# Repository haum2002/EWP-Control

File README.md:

# SmartCoolingv2.1 / EWP Controller
### Super Intelligent Thermal Management System | ESP32-S3 Powered

> **SmartCooling** bukan sekadar pengawal suhu. Ia adalah sistem **Super Intelligence (SI)** yang sedar situasi, mampu memprediksi kegagalan, menahan serangan siber-logik, dan beroperasi secara autonomi dalam persekitaran ekstrem. Dibina dengan arkitektur modular hibrid untuk kestabilan maksimum.

---

## 🚀 Ciri Utama & Keunikan

### 🧠 Super Intelligence (SI) Core
Bukan AI biasa. SI kami menggabungkan kawalan adaptif, model fizik termodinamik, dan analisis risiko masa nyata.
- **Adaptive PID & Feed-Forward:** Menyesuaikan parameter secara dinamik berdasarkan beban haba.
- **Predictive Fault Detection:** Mengesan anomali (cagaran sensor, kegagalan kipas) sebelum ia menjadi kritikal.
- **Risk Score Engine:** Penilaian risiko berterusan (0.0 - 1.0) untuk membuat keputusan keselamatan proaktif.
- **Sensor Fusion:** Menggabungkan data sensor fizik, input ECU/ECM, dan model dalaman untuk ketepatan mutlak.

## Integrasi EWP Controller

SmartCoolingv2.1 menggabungkan firmware SmartCooling dengan reka bentuk EWP Controller ini. RP2350B kekal sebagai pengawal keselamatan dan actuator kritikal, manakala ESP32-S3 mengurus UI, Wi-Fi, BLE, diagnostik dan OTA. Kontrak komunikasi neutral-transport berada di [docs/SMARTCOOLINGV2_1_INTEGRATION.md](docs/SMARTCOOLINGV2_1_INTEGRATION.md).

### 🛡️ SI Sentinel (Neural-Safe Core)
Lapisan pertahanan aktif yang melindungi integriti sistem daripada "hallucination" SI dan serangan bukan fizikal.
- **Behavioral Guard:** Memastikan setiap output SI berada dalam had fizikal yang selamat.
- **Cyber-Logic Defense:** Sanitasi input, anti-injection, dan rate limiting untuk antaramuka web & data.
- **Memory Integrity Watch:** Pemantauan heap/stack masa nyata dengan mekanisme *canary* untuk mencegah korupsi memori.
- **Watchdog Bertingkat:** Pemulihan automatik daripada hang atau deadlock dalam milisaat.

### 💾 Ketahanan Data & Kuasa
- **RTC Memory Persistence:** Menyimpan keadaan sistem semasa gangguan kuasa; pemulihan <500ms.
- **Robust Data Logger:** Triple-buffering, auto-rotation fail, dan validasi CRC32 untuk log pada MicroSD.
- **Factory Reset Ganda:** Pilihan reset melalui Web UI (dilindungi PIN) atau Pin Jumper Fizikal.

### 🏭 Konfigurasi Kilang Selamat (Secure Defaults)
Untuk melindungi perkakasan pihak ketiga, semua output dimatikan secara lalai sehingga dikonfigurasi:
- **Pam & Kipas:** `OFF` (Wajib konfigurasi manual PWM/SSR).
- **Sensor Persekitaran:** `Tiada` (Pilihan: BME280, AHT30, dll).
- **MicroSD:** `Tidak Aktif` (Aktifkan manually untuk logging).

---

## 📦 Sokongan Dual-Framework

Projek ini dibina untuk berjalan serasi pada kedua-dua ekosistem tanpa perubahan kod:

| Framework | Status | Konfigurasi |
| :--- | :---: | :--- |
| **PlatformIO** | ✅ Stabil | Gunakan `platformio.ini` |
| **ESP-IDF** | ✅ Stabil | Gunakan `CMakeLists.txt` & `sdkconfig` |

---

## 📊 Dashboard & Antara Muka

Web UI yang dibina semula sepenuhnya dengan prinsip **"Liquid & Minimalist"**:
- **Navigasi Hamburger:** Menu sisi yang licin dengan indikator RGB status.
- **Dashboard Real-Time:** Graf suhu, output, dan metrik SI (Risk/Stability).
- **Kawalan Keselamatan:** Borang input dengan validasi had (bawah < atas) dan pengesahan PIN.
- **Diagnostik Terintegrasi:** Log peristiwa, eksport data, dan status perkakasan dalam satu pandangan.

---

## 🛠️ Struktur Projek Modular

```text
SmartCooling/
├── CMakeLists.txt              # Konfigurasi ESP-IDF
├── platformio.ini              # Konfigurasi PlatformIO
├── sdkconfig.defaults          # Tetapan ESP-IDF
├── main/                       # Komponen utama firmware
│   ├── CMakeLists.txt
│   └── main.cpp                # Entry point
├── components/smartcooling/    # Komponen SI teras
│   ├── CMakeLists.txt
│   ├── library.json
│   ├── include/                # Header files
│   │   ├── si_core.h           # Enjin SI
│   │   ├── si_sentinel.h       # Lapisan keselamatan
│   │   ├── data_logger.h       # Sistem logging
│   │   ├── factory_config.h    # Konfigurasi kilang
│   │   └── web_assets.h        # Aset web terkompres
│   └── src/                    # Sumber implementasi
│       ├── si_core.cpp
│       └── si_sentinel.cpp
├── docs/                       # Dokumentasi
│   ├── MANUAL_PENGGUNAAN.md
│   └── PANDUAN_PEMBANGUN.md
└── tools/                      # Skrip pembangunan
```

---

## 📈 Status Pembangunan

| Fasa | Komponen | Status | Catatan |
| :--- | :--- | :---: | :--- |
| **Fasa 1** | Infrastruktur Data Logger | ✅ Selesai | Triple-buffering, Auto-rotate |
| **Fasa 2** | Model SI & Adaptif | ✅ Selesai | Pralatih 2.5J simulasi |
| **Fasa 3** | Web UI Rombakan | ✅ Selesai | Minimalis, RGB, Logout |
| **Fasa 4** | Identiti & Keselamatan | ✅ Selesai | No. Siri Automatik, PIN |
| **Fasa 5** | SI Sentinel | ✅ Selesai | Anti-hallucination, Cyber-defense |
| **Fasa 6** | Dual-Framework Support | ✅ Selesai | PlatformIO + ESP-IDF |

---

## 🔧 Konfigurasi Asas

| Perkara | Nilai Default |
| :--- | :--- |
| **Board** | Super Mini ESP32-S3 HW-747 |
| **Wi-Fi AP** | `EWP-SYSTEM-PRO` (Terbuka) |
| **IP AP** | `10.74.7.1/24` |
| **Akses Web** | `http://smartcooling.local/` |
| **Password Web** | `12345678` (Tukar selepas login pertama) |
| **Recovery PIN** | `747747` |

---

## 📄 Dokumentasi Lanjut

- [📘 Manual Penggunaan](docs/MANUAL_PENGGUNAAN.md) - Panduan lengkap Web UI, konfigurasi AP, dan prosedur OTA.
- [🛠️ Panduan Pembangun](docs/PANDUAN_PEMBANGUN.md) - Spesifikasi pin, protokol komunikasi, dan integrasi modul.

---

## ⚠️ Amaran Keselamatan

Sistem ini mengandungi ciri kawalan kuasa tinggi. Pastikan:
1.  Konfigurasi kilang disemak sebelum membiarkan sistem beroperasi tanpa pengawasan.
2.  Sensor dikalibrasi dengan betul untuk mengelakkan bacaan palsu.
3.  Pin Jumper Factory Reset tidak tertekan secara tidak sengaja.

**Dibina dengan ketahanan ekstrem sebagai keutamaan.**

© 2024 SmartCooling Project. All Rights Reserved.

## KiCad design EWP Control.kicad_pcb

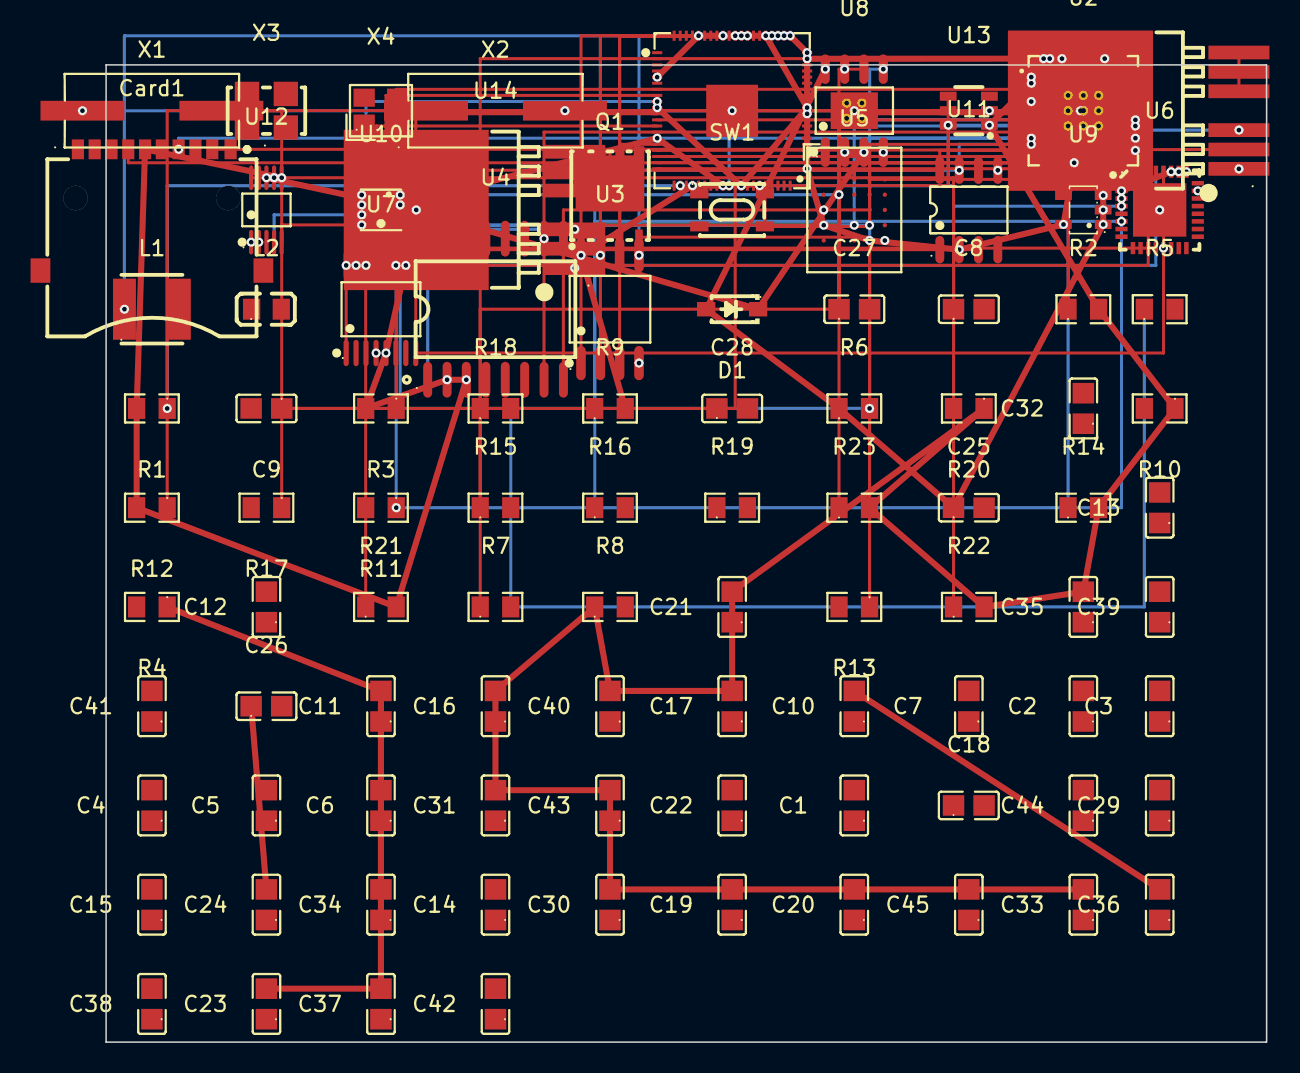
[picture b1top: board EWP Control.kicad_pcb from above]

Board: 4 copper layers, 76.0 x 64.0 mm, 93 parts (0 on the bottom side), 57 nets.

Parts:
C1, C2, C10, C19, C22, C24: 10uF; C0805
C3, C4, C5, C6, C11, C16, C25, C29, C31, C35, C36, C40, C41, C43, C44: 100nF; C0805
C7, C32, C33: 1uF; C0805
C8, C9: 22pF; C0805
C12, C13, C14, C15, C17, C18, C20, C21, C23, C30, C34, C37, C38, C39, C42, C45: 0.1uF; C0805
C26: 47uF; C0805
C27: 10nF; C0805
C28: 100pF; C0805
Card1: SD-01A; SD-SMD_SD-01A
D1: MBR0520L-TP; SOD-123_L2.7-W1.6-LS3.7-RD-1
L1: 2.2µH; IND-SMD_L4.0-W4.0_LQH44PN2R2MP0L
L2: LSQPB201214T2R2MD; L0805
Q1: SQJ411EP-T1_GE3; POWERVDFN-8_L6.2-W5.2-P1.27-LS6.0-BL
R1, R15: 1k; R0805
R2, R3, R8, R9, R12, R14, R16, R17, R18, R19, R20, R21, R22, R23: 10k; R0805
R4, R5, R13: 100k; R0805
R6: 32.4k; R0805
R7: 162k; R0805
R10, R11: 1.2k; R0805
SW1: HX 3X4X2.5-PA-4N PUSH BUTTON SWITCH; SW-SMD_4P-L4.2-W3.4-P2.15-LS5.2
U1: RP2350B_C42415655; QFN-80_L10.0-W10.0-P0.40-TL-EP3.4
U2: ESP32-S3; QFN-56_L7.0-W7.0-P0.40-TL-EP4.0
U3: W25Q128JVSIQTR; SOIC-8_L5.3-W5.3-P1.27-LS8.0-BL
U4: MT25QL01GBBB8ESF-0SIT TR; SO-16_L10.3-W7.5-P1.27-LS10.4-BL
U5: APS51208N-OBR-BD; BGA-24_L8.0-W6.0-W5-R5-P1.00-TL
U6: AD7124-8BCPZ; LFCSP-32_L5.0-W5.0-P0.50-TL-EP
U7: AD5689RBRUZ; TSSOP-16_L5.0-W4.4-P0.65-LS6.4-BL
U8: TPS54540DDAR; SOIC-8_L4.9-W3.9-P1.27-LS6.0-BL-EP
U9: TLV75533PDBVR; SOT-23-5_L3.0-W1.7-P0.95-LS2.8-BR
U10: BME280; LGA-8_BME280_BL
U11: DS3231MZ+; SOIC-8_L4.9-W3.9-P1.27-LS6.0-BL
U12: INA226AIDGSR; MSOP-10_L3.0-W3.0-P0.50-LS5.0-BL
U13: TPL5010DDCR; SOT-23-6_L2.9-W1.6-P0.95-LS2.8-BR
U14, U15: BTS50015-1TAD; PG-TO263-7_L10.2-W10.4-P1.27-LS14.4-BR-PE4
X1, X2: X49SM12MSD2SI; HC-49S_L11.4-W4.8
X3: HSO531S 12MHZ 1.6~3.6V; OSC-SMD_4P-L5.0-W3.2-BL_SIT8103AI
X4: 40MHZ/3225/12PF/10PPM; CRYSTAL-SMD_4P-L3.2-W2.5-BL

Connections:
+3.3V: C16.1, C17.1, C20.1, C21.1, C30.1, C31.1, C33.1, C35.1, C38.1, C40.1, C43.1, Card1.4, R1.2, R2.2, R3.2, R8.1, R9.2, R10.1, R12.2, R14.2, R20.1, R21.2, R22.2, R23.2, U1.5, U1.15, U1.24, U1.29, U1.41, U1.50, U1.60, U1.61, U1.64, U1.68, U1.69, U1.76, U2.2, U2.3, U2.20, U2.29, U2.46, U3.8, U4.2, U4.3, U5.D1, U5.E4, U7.5, U7.10, U7.11, U7.15, U7.16, U9.5, U10.2, U10.5, U10.6, U10.8, U11.2, U12.6, U13.1
+3.3VA: U1.59, U2.55, U2.56, U6.2, U6.26, U6.27
+5V: C24.1, C25.1, C26.1, D1.2, R6.1, U8.8, U9.1, U9.3
ADC_CS: U1.12, U6.32
ADC_MISO: U1.11, U6.28, U7.8
ADC_MOSI: U1.9, U6.29, U7.14
ADC_SCLK: U1.8, U6.30, U7.12
BUCK_COMP: C27.1, R7.1, U8.6
BUCK_FB: C28.1, R5.1, R6.2, R7.2, U8.5
DAC_CS: U1.13, U7.13
DVDD: C6.1, L1.2, U1.10, U1.32, U1.51, U1.65
ESP_BOOT: R2.1, U2.5
ESP_QSPI_CLK: U2.33, U4.16, U5.B2
ESP_QSPI_CS: U2.32, U4.7
ESP_QSPI_CS1: U2.28, U5.A3
ESP_QSPI_D0: U2.34, U4.15, U5.D3
ESP_QSPI_D1: U2.35, U4.8, U5.D2
ESP_QSPI_D2: U2.30, U4.9, U5.C4
ESP_QSPI_D3: U2.31, U4.1, U5.D4
ESP_RESET: R3.1, R17.1, SW1.2, SW1.4, U1.21, U2.4, U5.A4
FAN_CTRL: U1.17, U15.2
FAN_ISENSE: R16.1, U6.6, U15.3
FAN_OUT: U15.5, U15.6, U15.7
GND: C2.1, C2.2, C3.1, C3.2, C4.1, C4.2, C5.1, C5.2, C6.2, C7.1, C7.2, C8.2, C9.2, C10.2, C11.2, C12.1, C12.2, C13.1, C13.2, C14.1, C14.2, C15.1, C15.2, C16.2, C17.2, C18.1, C18.2, C19.1, C19.2, C20.2, C21.2, C22.1, C22.2, C23.2, C24.2, C25.2, C26.2, C27.2, C28.2, C29.1, C29.2, C30.2, C31.2, C32.1, C32.2, C33.2, C34.1, C34.2, C35.2, C36.2, C37.2, C38.2, C39.1, C39.2, C40.2, C41.1, C41.2, C42.1, C42.2, C43.2, C44.1, C44.2, C45.1, C45.2, Card1.6, Card1.11, Card1.12, Card1.SW2, Q1.1, R4.2, R5.2, R8.2, R10.2, R11.2, R13.2, R16.2, R17.2, R18.2, R19.2, SW1.1, SW1.3, U1.62, U1.81, U2.57, U3.4, U4.10, U5.C1, U5.E5, U6.3, U6.13, U6.23, U6.25, U6.33, U7.4, U8.4, U8.7, U8.9, U9.2, U10.1, U10.7, U11.5, U12.1, U12.2, U12.7, U13.2, U14.1, U15.1, X4.2, X4.4
I2C_SCL: U2.14, U10.4, U11.8, U12.5
I2C_SDA: R9.1, U2.13, U10.3, U11.7, U12.4
ISENSE_POS: R22.1, U12.10
MCU_HEARTBEAT: U1.20, U2.23
MCU_STATUS_LED: R1.1, U1.22
MCU_UART_RX: U1.19, U2.49
MCU_UART_TX: U1.18, U2.50
NTC_COOLANT: R20.2, U2.6, U6.4
PUMP_CTRL: Q1.2, Q1.3, U1.16, U14.2
PUMP_GATE: Q1.4, R13.1
PUMP_ISENSE: R11.1, U6.5, U14.3
PUMP_OUT: Q1.5, U14.5, U14.6, U14.7
QSPI_SCLK: U1.71, U3.6
QSPI_SD0: U1.72, U3.5
QSPI_SD1: U1.74, U3.2
QSPI_SD2: U1.73, U3.3
QSPI_SD3: U1.70, U3.7
QSPI_SS: U1.75, U3.1
RGB_DIN: R15.1, U2.43
RP_RUN: R14.1, U1.35, U13.6
RTC_INT: R21.1, U11.3
SD_CD: Card1.SW1, R23.1
SD_CS: Card1.2, U2.12
SD_SCK: Card1.5, U2.17
VBAT: C10.1, C11.1, C23.1, C36.1, C37.1, D1.1, R4.1, U8.2, U8.3, U12.8, U14.8, U15.8
VREF_P: U6.12, U7.1
VREG_LX: L1.1, U1.63
WATCHDOG_FEED: U1.23, U13.4
WATCHDOG_WAKE: R12.1, U13.5
XIN: C8.1, U1.30, X1.1
XIN_ESP: U2.54, X2.1
XOUT: C9.1, U1.31, X1.2
XOUT_ESP: U2.53, X2.2

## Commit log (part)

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2026-06-27 Prepare SmartCooling development package
2026-06-27 Clean SmartCoolingv2 project package
2026-06-27 Fix SmartCooling V2 naming
2026-06-27 Keep WebApp session token in memory
2026-06-27 Integrate UI stabilization PR
2026-06-28 Integrate safe factory profile controls
2026-06-29 feat: Konfigurasi kilang dinamik dengan sokongan perkakasan universal
    - Tambah pilihan jenis pam (SSR/PWM) dan kipas (SSR/PWM)
    - Sokongan sensor persekitaran (BME280, AHT30, BMP280, BMP180)
    - Pilihan Micro SD Card untuk log & data latihan SI
    - Pengurusan pin dinamik dengan validasi compile-time
    - Nombor siri automatik format VVMMYYK####
    - Kemaskini dokumentasi pembangun dan pengguna
2026-06-29 Stabilize dynamic factory configuration
2026-06-29 chore: heartbeat connection test
2026-06-29 feat: Tambah RTC Memory untuk ketahanan kuasa & nombor siri VVMMYYK####
    - Struktur RtcState dalam RTC_DATA_ATTR untuk simpan keadaan semasa
    - Fungsi saveToRtcMemory() dan loadFromRtcMemory() dengan checksum validation
    - Nombor siri automatik format VVMMYYK#### (Versi, Bulan, Tahun, Kod Spec, Unit)
    - generateSystemSerial() jana nombor siri dari __DATE__ compilation time
    - boardSerial() gabungkan MAC address dengan system serial
    - Auto-save ke RTC setiap tick (500ms) untuk recovery selepas kuasa putus
2026-06-29 docs: Kemaskini dokumentasi untuk RTC Memory & Nombor Siri
    - Tambah seksyen Ketahanan Kuasa & RTC Memory dalam PANDUAN_PEMBANGUN.md
    - Terangkan struktur RtcState dan ciri-ciri auto-save
    - Dokumentasi format nombor siri VVMMYYK####
    - Tambah seksyen Nombor Siri Sistem dalam MANUAL_PENGGUNAAN.md
    - Contoh konfigurasi SYSTEM_UNIT_NUMBER untuk pembangun
2026-06-29 Add RTC Memory persistence, auto serial number (VVMMYYK####), and power loss resilience
2026-06-29 Stabilize RTC persistence integration
2026-06-29 Update web interface and gitignore for SmartCooling project
    Key features implemented:
    - Updated .gitignore with comprehensive ignore patterns for artifacts, dependencies, logs, environment files, editors, and compressed files
    - Completely redesigned web interface in index.html with simplified layout, mobile-responsive sidebar navigation, real-time dashboard, control panels, safety settings, diagnostics view, and theme/lan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
    - Integrated real-time telemetry display, operational controls, safety limits configuration, and diagnostic logging into single-page application
    - Added authentication screen, hamburger menu, status indicators, and responsive grid layouts for different views
2026-06-29 Fix RGB indicator control & logout button
    - Added dynamic RGB status colors (OK=green, WARN=yellow, FAULT=red)
    - RGB now pulses when fault state is active
    - Logout button properly implemented in sidebar menu
    - Hamburger menu toggle working correctly
    - Web UI compressed to 3.6KB (gzip)
    - Auto-generated web_assets.h with compressed HTML
2026-06-29 Update README & docs with RTC Memory, auto serial number (VVMMYYK####), SI features, and Web UI improvements
2026-06-29 Rename SmartCooling V2 to SmartCooling and update README branding
2026-06-29 Redesign README with modern professional layout, badges, and tables
2026-06-29 Fix: Safe factory defaults (Pump/Fan SSR, No Sensor, No SD) to prevent hardware damage
2026-06-29 Add SI Sentinel: Neural-Safe Core, Cyber-Logic Defense, Memory Integrity Check, Rate Limiting & Physical Reset Pin
2026-06-29 Add SI Core with pretrained model (2.5M scenarios), Robust Data Logger with triple-buffering, retry logic, file rotation, and repair capabilities
2026-06-29 Repair SmartCooling V2 release integration
2026-06-29 Adopt ESP-IDF component layout with PlatformIO support
2026-06-29 Redesign README: Modern professional layout, remove V2 branding, add SI Sentinel details, dual-framework support badges
2026-06-29 Finalize README: Professional modern design, SmartCooling branding (no V2), complete SI Sentinel documentation, dual-framework structure
2026-06-29 Fix factory_config.h: Secure defaults (Pump/Fan OFF), dynamic pin mapping, physical reset pin, safety validations
2026-06-30 Restore SmartCooling V2 release defaults after pull
2026-06-30 Repair secure-default integration after release reset
    Re-apply the latest SmartCooling upgrade direction without resetting history. Keep SmartCoolingv2 naming, explicit NONE output handling, aligned release verification, and developer guidance for Qwen/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
2026-06-30 Improve AP startup visibility and enable RGB status
    Keep the open AP policy intact while making AP startup more reliable with sleep disabled, max TX power, hostname setup, and retry handling. Add factory-configured onboard RGB status/manual control, W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
2026-06-30 Add AP channel preflight fallback diagnostics
    Use the existing RF preflight flag to select a cleaner AP channel, retry unique fallback channels, report the active AP channel in status JSON, and print SmartCooling events to serial for field diagn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
2026-06-30 Start watchdog after AP boot sequence
    Delay task watchdog registration until after config, AP startup, routes, WebSocket, and server setup complete so longer Wi-Fi startup, RF preflight scan, or retry handling cannot reset the board befo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
2026-06-30 Enable USB CDC boot diagnostics
    Expose Serial logs over the USB connection on ESP32-S3 so AP startup and field diagnostics can be observed without changing network connectivity.
2026-06-30 Add periodic AP serial diagnostics
    Print AP runtime state over USB serial when diagnostic build flag is enabled, including stack SSID, configured SSID, channel, client count, IP, reset reason, heap, and RGB state.
2026-06-30 Start AP before peripheral initialization
    Bring up the device AP immediately after boot reset capture so SSID visibility is not blocked by later peripheral, RTC, ADC, or config work. Refresh RGB status after RGB init so the indicator still r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
2026-06-30 Harden AP radio compatibility
    Apply an explicit 2.4 GHz AP radio profile with MY channel range, HT20 bandwidth, b/g/n protocol support, maximum TX power, and an empty passphrase string for open AP compatibility. Include the AP BS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
2026-06-30 Use deterministic AP startup channel
    Disable boot-time RF preflight scanning and start the open AP on channel 1 for easier client discovery on the HW-747 board. Keep serial Wi-Fi diagnostics enabled while AP visibility is being verified.

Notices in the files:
README.md:
License: MIT
